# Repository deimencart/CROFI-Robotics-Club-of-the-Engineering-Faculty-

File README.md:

# 🤖 Robotics Club Project Portfolio

> This repository gathers all the robotics-related projects I developed and contributed to as part of the **Robotics Club**. It serves as a personal archive, a technical reference, and a showcase of my hands-on experience in embedded systems, control, automation, and robot design.

---

## 📦 Repository Purpose

This is the **central repository** for:
- 📂 Uploading and organizing my robotics projects
- 🧠 Documenting hardware & software contributions
- 🛠️ Sharing schematics, PCB designs, Arduino/ROS code
- 📸 Storing images, build logs, and test documentation

Each folder contains:
- 📝 A dedicated `README.md` with description and instructions
- 💾 Code files and firmware
- 📐 Schematic and PCB files
- 📸 Photos and media (builds, demos, results)

---

## 🧠 What You’ll Find

- **Microcontroller Integration**: Arduino, ESP32
- **Motor Control**: PWM, H-bridge, PID
- **ROS Prototyping**: Basic nodes and hardware interfaces
- **PCB Design**: Eagle-based custom boards
- **Sensor Use**: IR, ultrasonic, encoders
- **Creative Robotics**: Art-meets-technology installations

---

## 🚀 Why This Matters

This repository reflects my:
- 🛠️ Practical engineering abilities
- 🔄 Iterative problem-solving mindset
- 🎓 Preparation for postgraduate studies in Robotics & AI
- 👥 Collaborative experience with multidisciplinary teams

---

## 👤 Author

**Diego Méndez Carter**  
Robotics Engineer | Component Specialist | Creative Technologist  

---

## 📜 License

All content in this repository is shared under the **MIT License**, unless stated otherwise in subdirectories.

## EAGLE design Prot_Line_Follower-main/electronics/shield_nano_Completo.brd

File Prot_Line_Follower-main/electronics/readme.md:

# 🛠️ Arduino Nano Motor Driver Shield (Custom PCB)

This project is a custom-designed shield for the **Arduino Nano**, tailored for compact robotic systems. The PCB integrates:
- Dual motor control via an L293D H-Bridge
- Button interface
- Power regulation circuitry
- Status LEDs
- A shape designed for easy integration into mobile platforms

---

## 🖥️ PCB Schematic

### 🔧 Main Features

- **Microcontroller**: Arduino Nano (modular socket)
- **Motor Driver**: L293D for 2-channel DC motor control
- **Power Supply**: Includes 5V regulator, capacitors for filtering
- **Buttons**: 2 push buttons with pull-down resistors
- **LED Indicators**: Power, logic, motor activity
- **Connectivity**: Header pins for I/O, power, and sensors

---

## 🖲️ PCB Layout

### ⚙️ Design Highlights

- **Form Factor**: Shaped to fit a robotic chassis; motor brackets visible
- **Compact Routing**: Traces efficiently routed to minimize space
- **Component Placement**:
  - Motors on each side
  - Arduino socket in the middle
  - Power regulator and capacitors at the lower center
  - LED indicators and buttons easily accessible on top surface
- **Mounting Holes**: For easy mechanical integration

---

## 📌 Pin Mapping Summary

| Arduino Nano Pin | Function           |
|------------------|--------------------|
| D3, D4           | Motor A direction  |
| D5, D6           | Motor B direction  |
| D9, D10          | Button inputs      |
| A0–A5            | Free for sensors   |
| VIN              | Motor power input  |
| +5V, GND         | Power distribution |

---

## ⚡ Power Section

- Input: 6V–12V through DC jack or terminal
- Regulated to +5V for logic and Arduino
- Filtered with 100µF and 220µF capacitors
- Diode protection included

---

## 🧰 Applications

This board is ideal for:
- Line-followers
- Mini autonomous vehicles
- PID control experiments
- Sensor + motor integration platforms

---

## 🔄 Future Enhancements

- Add screw terminals for battery/motor connection
- Reverse polarity protection
- Add sensor breakout pins for I2C modules

---

## 👤 Author

**Diego Méndez Carter**  
Component Engineer & Robotics Enthusiast  
## 📜 License

MIT License — feel free to use, modify, and share.

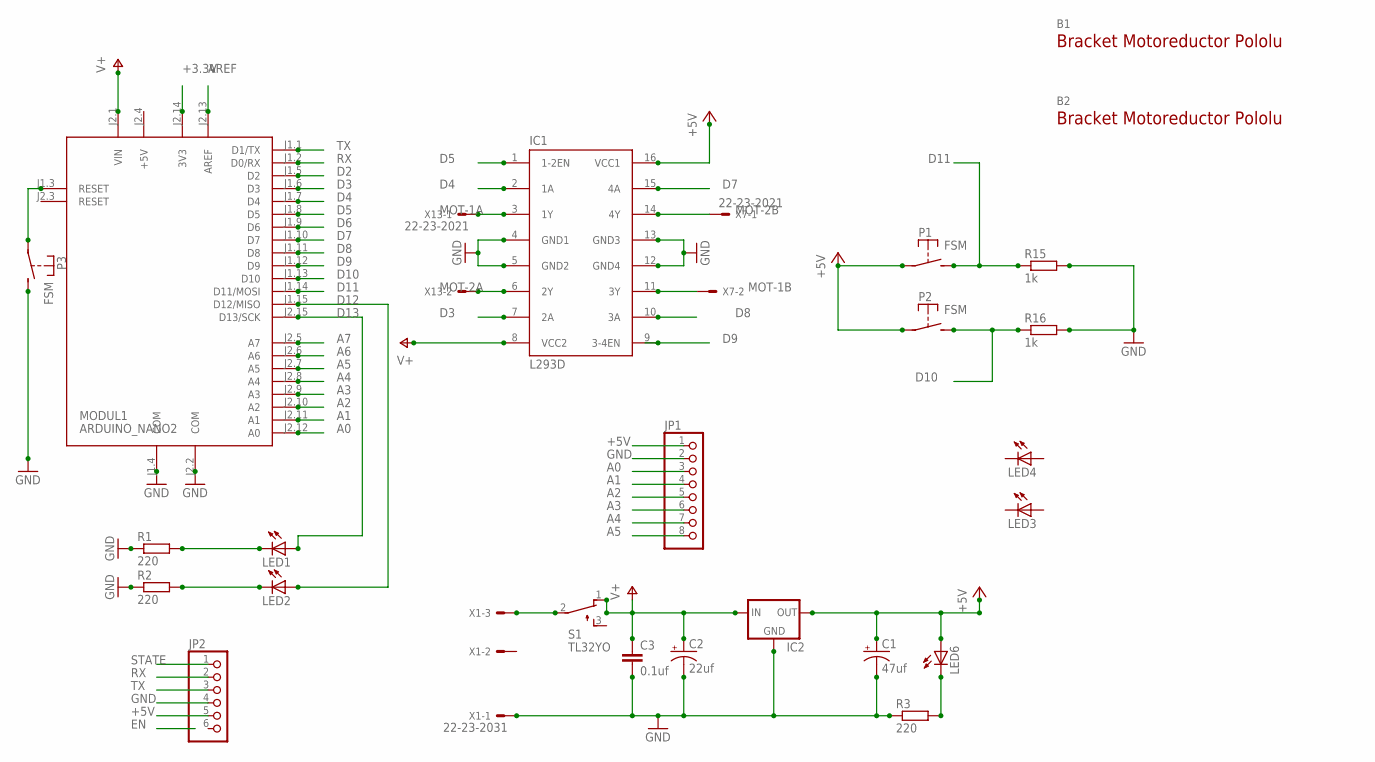
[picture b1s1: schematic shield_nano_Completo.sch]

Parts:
B1, B2: BRACKET-MOTOR-REDUCTOR-POLOLU; BRACKET-MOTORREDUCTOR-POLOLU
C1: 47uf; CPOL-RADIAL-100UF-25V
C2: 22uf; CPOL-RADIAL-100UF-25V
C3: 0.1uf; C025-030X050
IC1: L293D; DIL16
IC2: V_REG_78XX-TO-220; TO-220-ALT
JP1: PINHD-1X8; 1X08
JP2: PINHD-1X6; 1X06
LED1, LED2, LED3, LED4, LED6: LED5MM
MODUL1: ARDUINO_NANO2
P1, P2, P3: FSM
R1, R2, R3: 220; 0204/5
R15, R16: 1k; 0204/5
S1: TL32YO; TL3XYO
X1: 22-23-2031
X7, X13: 22-23-2021

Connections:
+3.3V: MODUL1.J2.14 (3V3)
+5V: C1.1 (+), IC1.16 (VCC1), IC2.OUT, JP1.1, JP2.5, LED6.A, MODUL1.J2.4 (+5V), P1.P$1, P2.P$1
A0: JP1.3, MODUL1.J2.12 (A0)
A1: JP1.4, MODUL1.J2.11 (A1)
A2: JP1.5, MODUL1.J2.10 (A2)
A3: JP1.6, MODUL1.J2.9 (A3)
A4: JP1.7, MODUL1.J2.8 (A4)
A5: JP1.8, MODUL1.J2.7 (A5)
A6: MODUL1.J2.6 (A6)
A7: MODUL1.J2.5 (A7)
AREF: MODUL1.J2.13 (AREF)
D2: MODUL1.J1.5 (D2)
D3: IC1.7 (2A), MODUL1.J1.6 (D3)
D4: IC1.2 (1A), MODUL1.J1.7 (D4)
D5: IC1.1 (1-2EN), MODUL1.J1.8 (D5)
D6: MODUL1.J1.9 (D6)
D7: IC1.15 (4A), MODUL1.J1.10 (D7)
D8: IC1.10 (3A), MODUL1.J1.11 (D8)
D9: IC1.9 (3-4EN), MODUL1.J1.12 (D9)
D10: MODUL1.J1.13 (D10), P2.P$2 (S), R16.1
D11: MODUL1.J1.14 (D11/MOSI), P1.P$2 (S), R15.1
D12: LED2.A, MODUL1.J1.15 (D12/MISO)
D13: LED1.A, MODUL1.J2.15 (D13/SCK)
GND: C1.2 (-), C2.2 (-), C3.2, IC1.4 (GND1), IC1.5 (GND2), IC1.12 (GND4), IC1.13 (GND3), IC2.GND, JP1.2, JP2.4, MODUL1.J1.4 (COM), MODUL1.J2.2 (COM), P3.P$2 (S), R1.1, R2.1, R3.1, R15.2, R16.2, X1.1
MOT-1A: IC1.3 (1Y), X13.1
MOT-1B: IC1.11 (3Y), X7.2
MOT-2A: IC1.6 (2Y), X13.2
MOT-2B: IC1.14 (4Y), X7.1
unnamed: S1.2, X1.3
unnamed: LED1.K (C), R1.2
unnamed: LED2.K (C), R2.2
unnamed: LED6.K (C), R3.2
unnamed: MODUL1.J1.3 (RESET), P3.P$1
RX: JP2.2, MODUL1.J1.2 (D0/RX)
STATE: JP2.1
TX: JP2.3, MODUL1.J1.1 (D1/TX)
V+: C2.1 (+), C3.1, IC1.8 (VCC2), IC2.IN, MODUL1.J2.1 (VIN), S1.1 (O)

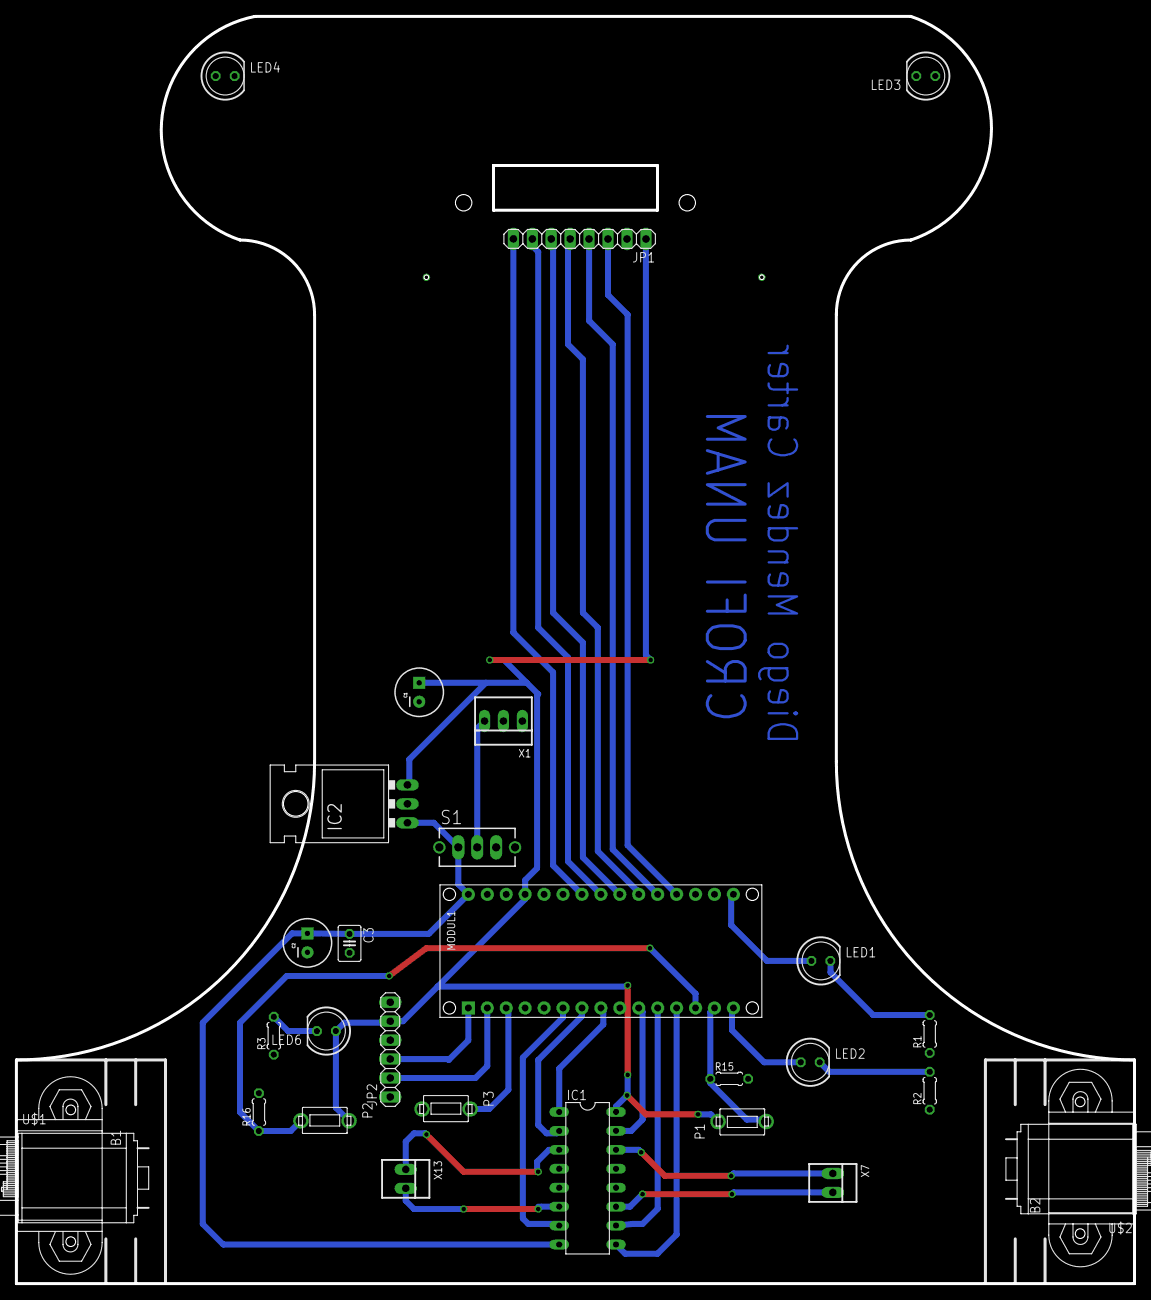
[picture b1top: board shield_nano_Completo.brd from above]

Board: 2 copper layers, 150.0 x 170.0 mm, 29 parts (0 on the bottom side), 30 nets.

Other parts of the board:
U$1, U$2: MOTOR-REDUCTOR-POLOLU

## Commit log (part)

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2025-04-13 Create Miscelaneus_Robots
2025-12-01 Update PCB layout section in readme
2025-12-01 Fix formatting for mentor name in readme

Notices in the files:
parts and their libraries:
SparkFun: Licensing: CC v3.0 Share-Alike You are welcome to use this library for commercial purposes.
